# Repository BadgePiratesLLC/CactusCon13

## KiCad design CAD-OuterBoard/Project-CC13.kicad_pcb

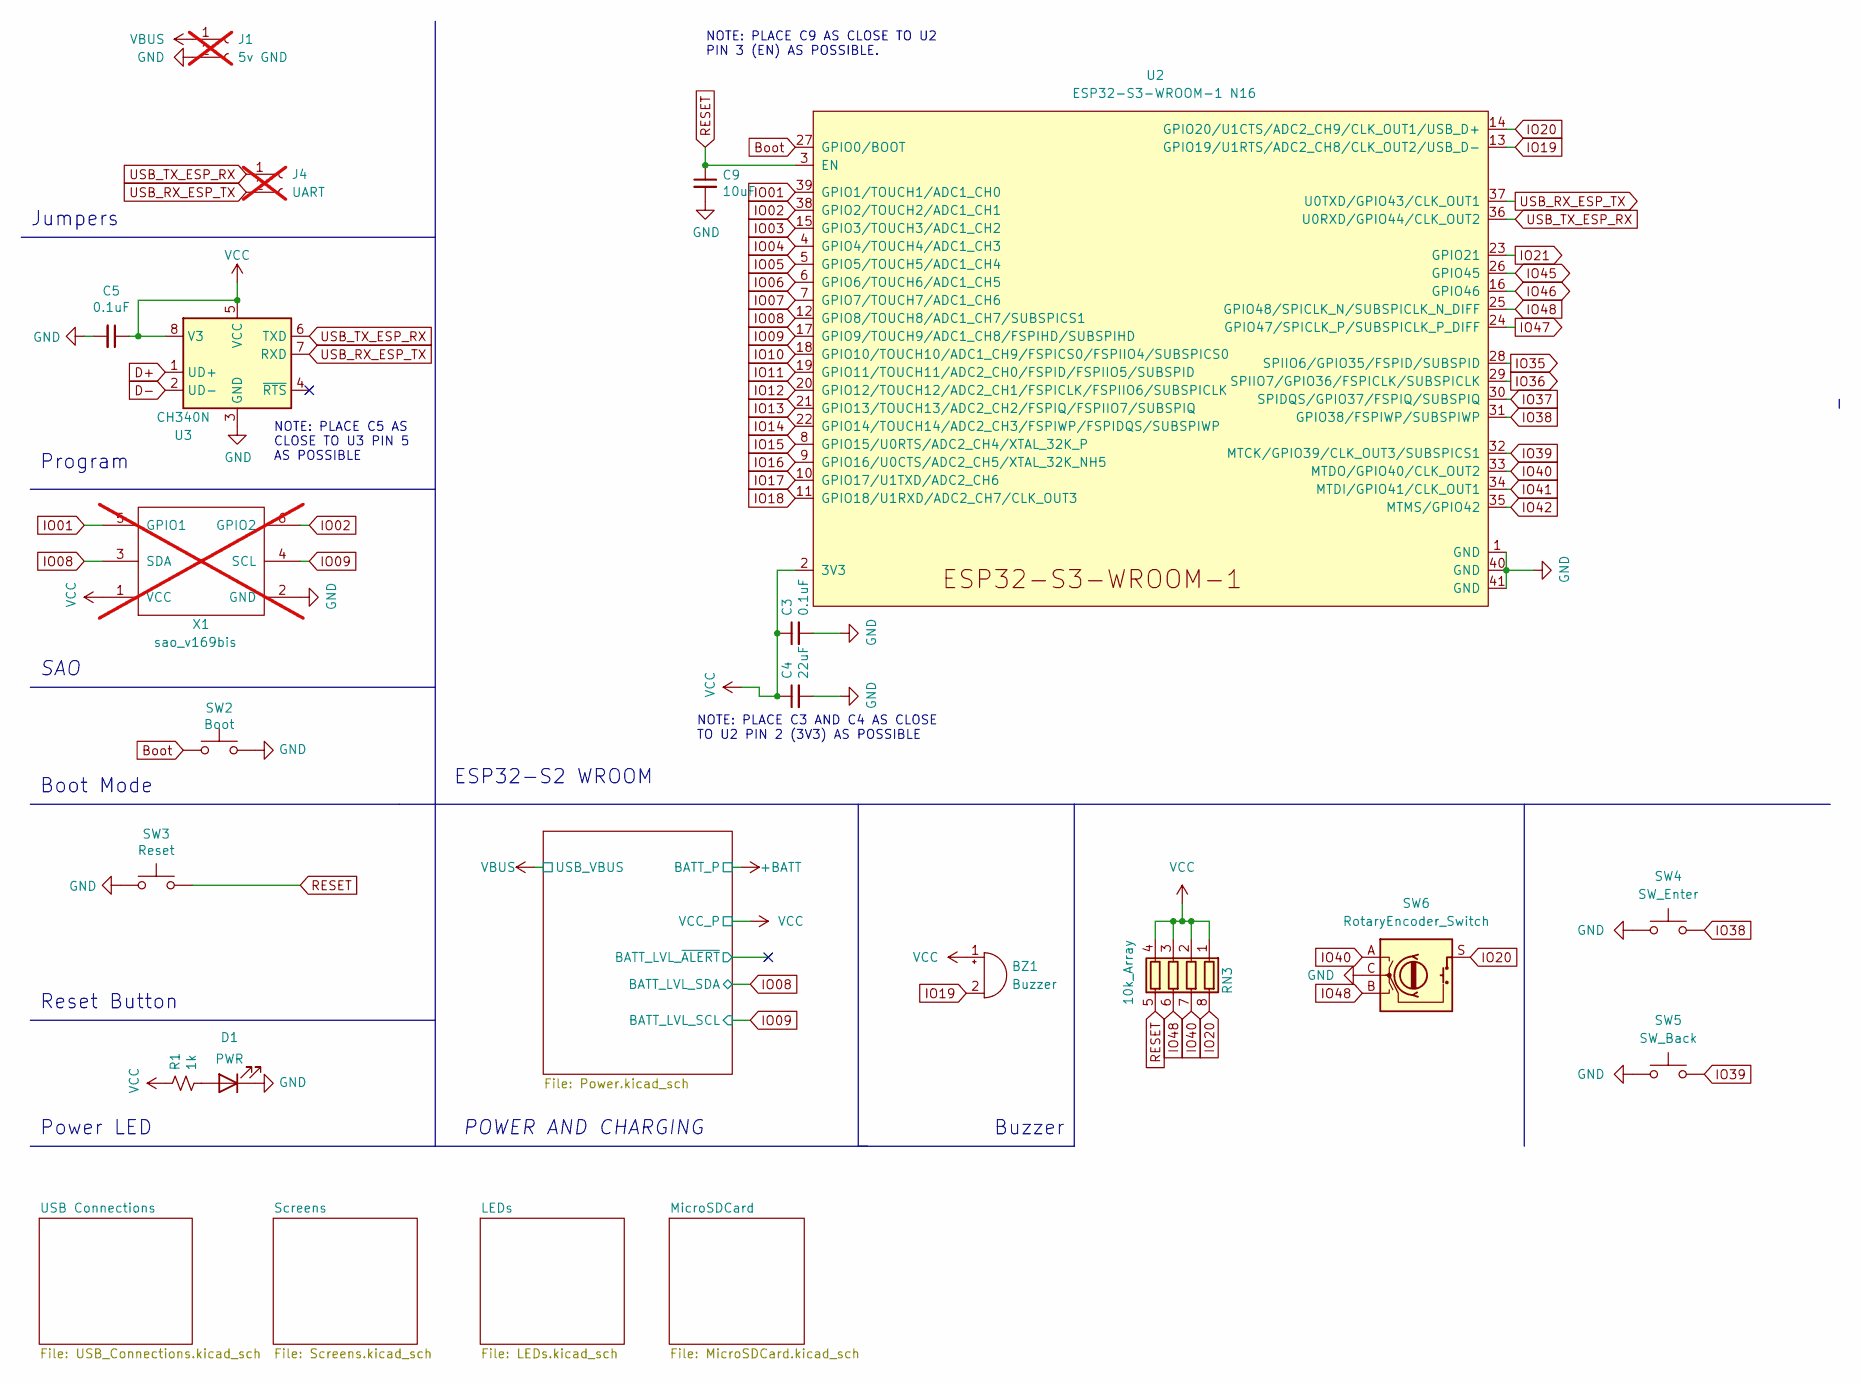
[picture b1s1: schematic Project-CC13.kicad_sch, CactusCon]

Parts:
BZ1: Buzzer; FUET-9032-Buzzer
C3, C5: 0.1uF; C_0805_2012Metric; MFG_PN CT41G-0805-2X1-50V-0.1μF-K(N)
C4: 22uF; C_0805_2012Metric; MFG_PN CL21A226MAYNNNE
C9: 10uF; C_0805_2012Metric; MFG_PN CL21A106KPCLQNC
D1: PWR; LED_1206; MFG_PN NCD1206C1
J1: 5v GND; PinHeader_1x02_P2.54mm_Vertical; not fitted
J4: UART; PinHeader_1x02_P2.54mm_Vertical; not fitted
R1: 1k; R_1206_3216Metric; MFG_PN RC1206FR-071KL
RN3: 10k_Array; R_Array_Convex_4x0603; MFG_PN YC164-RR-0710KL
SW2: Boot; Switch_Tactile_SMD_B3U-1000P-BPVersion; MFG_PN B3U-1000P
SW3: Reset; Switch_Tactile_SMD_B3U-1000P-BPVersion; MFG_PN B3U-1000P
SW4: SW_Enter; SW_SPST_TL3305C(small)
SW5: SW_Back; SW_SPST_TL3305C(small)
SW6: RotaryEncoder_Switch; SIQ-02FVS3_Encoder
U2: ESP32-S3-WROOM-1 N16; ESP32-S3-WROOM-1; MFG_PN ESP32-S3-WROOM-1-N8R8
U3: CH340N; SOIC-8-1EP_W3.9mm; MFG_PN CH340N
X1: sao_v169bis; Badgelife-SAOv169-SAO_Side_B.SLK; not fitted

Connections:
Boot: SW2.1, U2.27 (GPIO0/BOOT)
D+: U3.1 (UD+); also elsewhere on the board
D-: U3.2 (UD-); also elsewhere on the board
GND: C3.2, C4.2, C5.2, C9.2, D1.1 (K), J1.2, SW2.2, SW3.1, SW4.1, SW5.1, SW6.C, U2.1 (GND), U2.40 (GND), U2.41 (GND), U3.3 (GND), X1.2 (GND); also elsewhere on the board
IO01: U2.39 (GPIO1/TOUCH1/ADC1_CH0), X1.5 (GPIO1)
IO02: U2.38 (GPIO2/TOUCH2/ADC1_CH1), X1.6 (GPIO2)
IO03: U2.15 (GPIO3/TOUCH3/ADC1_CH2); also elsewhere on the board
IO04: U2.4 (GPIO4/TOUCH4/ADC1_CH3); also elsewhere on the board
IO05: U2.5 (GPIO5/TOUCH5/ADC1_CH4); also elsewhere on the board
IO06: U2.6 (GPIO6/TOUCH6/ADC1_CH5); also elsewhere on the board
IO07: U2.7 (GPIO7/TOUCH7/ADC1_CH6); also elsewhere on the board
IO08: U2.12 (GPIO8/TOUCH8/ADC1_CH7/SUBSPICS1), X1.3 (SDA); also elsewhere on the board
IO09: U2.17 (GPIO9/TOUCH9/ADC1_CH8/FSPIHD/SUBSPIHD), X1.4 (SCL); also elsewhere on the board
IO10: U2.18 (GPIO10/TOUCH10/ADC1_CH9/FSPICS0/FSPIIO4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); also elsewhere on the board
IO11: U2.19 (GPIO11/TOUCH11/ADC2_CH0/FSPID/FSPIIO5/S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); also elsewhere on the board
IO12: U2.20 (GPIO12/TOUCH12/ADC2_CH1/FSPICLK/FSPIIO6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); also elsewhere on the board
IO13: U2.21 (GPIO13/TOUCH13/ADC2_CH2/FSPIQ/FSPIIO7/S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); also elsewhere on the board
IO14: U2.22 (GPIO14/TOUCH14/ADC2_CH3/FSPIWP/FSPIDQS/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); also elsewhere on the board
IO15: U2.8 (GPIO15/U0RTS/ADC2_CH4/XTAL_32K_P); also elsewhere on the board
IO16: U2.9 (GPIO16/U0CTS/ADC2_CH5/XTAL_32K_NH5); also elsewhere on the board
IO17: U2.10 (GPIO17/U1TXD/ADC2_CH6); also elsewhere on the board
IO18: U2.11 (GPIO18/U1RXD/ADC2_CH7/CLK_OUT3); also elsewhere on the board
IO19: BZ1.2 (+), U2.13 (GPIO19/U1RTS/ADC2_CH8/CLK_OUT2/USB_D-)
IO20: RN3.8 (R1.2), SW6.S, U2.14 (GPIO20/U1CTS/ADC2_CH9/CLK_OUT1/USB_D+); also elsewhere on the board
IO21: U2.23 (GPIO21); also elsewhere on the board
IO35: U2.28 (SPIIO6/GPIO35/FSPID/SUBSPID); also elsewhere on the board
IO36: U2.29 (SPIIO7/GPIO36/FSPICLK/SUBSPICLK); also elsewhere on the board
IO37: U2.30 (SPIDQS/GPIO37/FSPIQ/SUBSPIQ); also elsewhere on the board
IO40: RN3.7 (R2.2), SW6.A, U2.33 (MTDO/GPIO40/CLK_OUT2); also elsewhere on the board
IO41: U2.34 (MTDI/GPIO41/CLK_OUT1)
IO42: U2.35 (MTMS/GPIO42)
IO45: U2.26 (GPIO45)
IO46: U2.16 (GPIO46); also elsewhere on the board
IO47: U2.24 (GPIO47/SPICLK_P/SUBSPICLK_P_DIFF); also elsewhere on the board
IO48: RN3.6 (R3.2), SW6.B, U2.25 (GPIO48/SPICLK_N/SUBSPICLK_N_DIFF); also elsewhere on the board
unnamed: D1.2 (A), R1.2
RESET: C9.1, RN3.5 (R4.2), SW3.2, U2.3 (EN)
USB_RX_ESP_TX: J4.2, U2.37 (U0TXD/GPIO43/CLK_OUT1), U3.7 (RXD)
USB_TX_ESP_RX: J4.1, U2.36 (U0RXD/GPIO44/CLK_OUT2), U3.6 (TXD)
VBUS: J1.1; also elsewhere on the board
VCC: BZ1.1 (-), C3.1, C4.1, C5.1, R1.1, RN3.1 (R1.1), RN3.2 (R2.1), RN3.3 (R3.1), RN3.4 (R4.1), U2.2 (3V3), U3.5 (VCC), U3.8 (V3), X1.1 (VCC); also elsewhere on the board

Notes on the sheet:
Buzzer
POWER AND CHARGING
SAO
Power LED
Jumpers
ESP32-S2 WROOM
NOTE: PLACE C5 AS CLOSE TO U3 PIN 5 AS POSSIBLE
Program
Boot Mode
NOTE: PLACE C3 AND C4 AS CLOSE TO U2 PIN 2 (3V3) AS POSSIBLE
Reset Button
NOTE: PLACE C9 AS CLOSE TO U2 PIN 3 (EN) AS POSSIBLE.

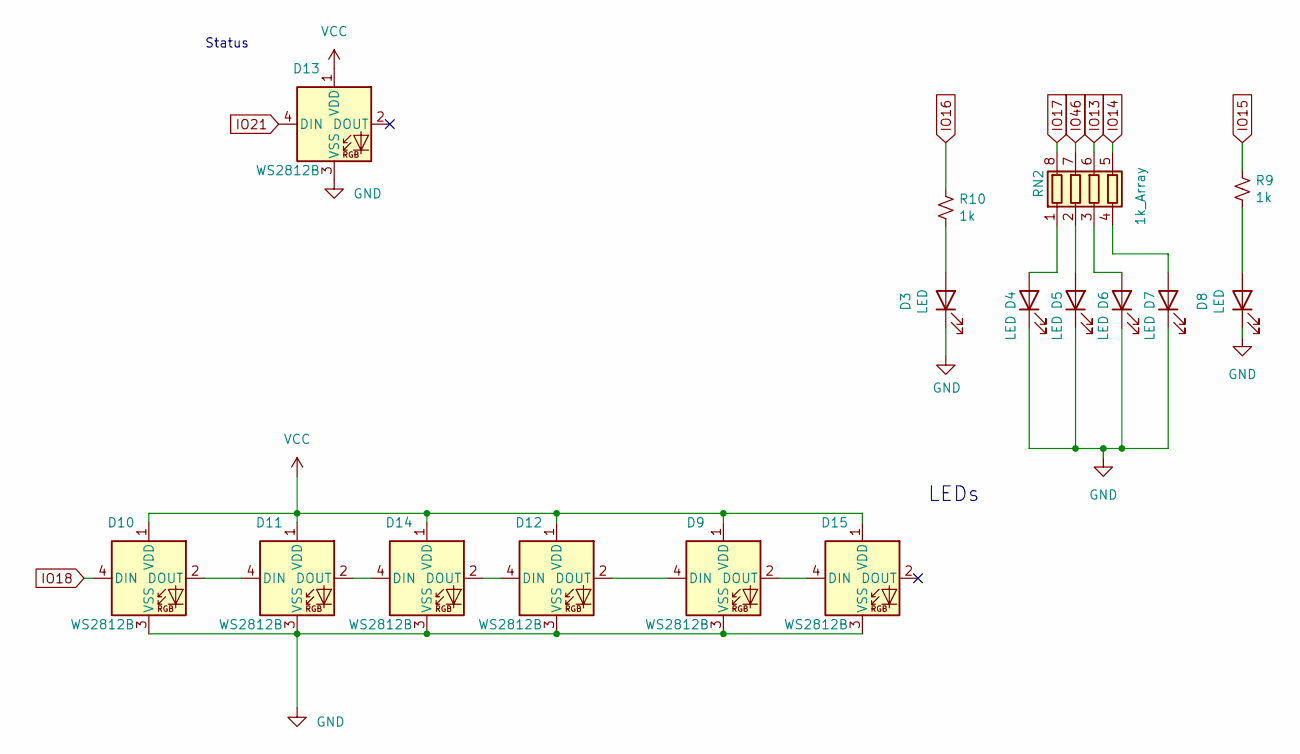
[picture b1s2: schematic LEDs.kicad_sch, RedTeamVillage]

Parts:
D3, D4, D5, D6, D7, D8: LED; LED_Osram_Lx_P47F_D2mm_ReverseMount_Proper_Mask Only; MFG_PN AA3528SYCKT09
D9, D10, D11, D12, D13, D14, D15: WS2812B; LED_WS2812B_PLCC4_5.0x5.0mm_P3.2mm; MFG_PN WS2812B-B/T
R9, R10: 1k; R_1206_3216Metric; MFG_PN RC1206FR-071KL
RN2: 1k_Array; R_Array_Convex_4x0603; MFG_PN YC164-JR-071KL

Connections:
GND: D3.1 (K), D4.1 (K), D5.1 (K), D6.1 (K), D7.1 (K), D8.1 (K), D9.3 (VSS), D10.3 (VSS), D11.3 (VSS), D12.3 (VSS), D13.3 (VSS), D14.3 (VSS), D15.3 (VSS); also elsewhere on the board
IO13: RN2.6 (R3.2); also elsewhere on the board
IO14: RN2.5 (R4.2); also elsewhere on the board
IO15: R9.1; also elsewhere on the board
IO16: R10.1; also elsewhere on the board
IO17: RN2.8 (R1.2); also elsewhere on the board
IO18: D10.4 (DIN); also elsewhere on the board
IO21: D13.4 (DIN); also elsewhere on the board
IO46: RN2.7 (R2.2); also elsewhere on the board
unnamed: D3.2 (A), R10.2
unnamed: D4.2 (A), RN2.1 (R1.1)
unnamed: D5.2 (A), RN2.2 (R2.1)
unnamed: D6.2 (A), RN2.3 (R3.1)
unnamed: D7.2 (A), RN2.4 (R4.1)
unnamed: D8.2 (A), R9.2
unnamed: D10.2 (DOUT), D11.4 (DIN)
unnamed: D11.2 (DOUT), D14.4 (DIN)
unnamed: D12.4 (DIN), D14.2 (DOUT)
unnamed: D9.4 (DIN), D12.2 (DOUT)
unnamed: D9.2 (DOUT), D15.4 (DIN)
VCC: D9.1 (VDD), D10.1 (VDD), D11.1 (VDD), D12.1 (VDD), D13.1 (VDD), D14.1 (VDD), D15.1 (VDD); also elsewhere on the board

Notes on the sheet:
LEDs
Status

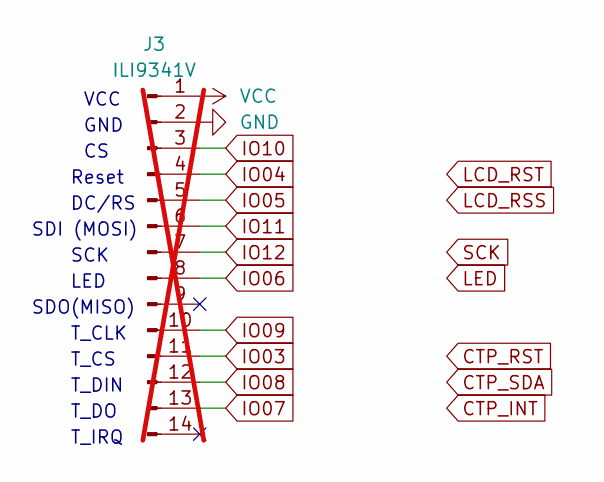
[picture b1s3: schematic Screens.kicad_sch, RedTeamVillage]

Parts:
J3: ILI9341V; PinHeader_1x14_P2.54mm_Vertical; not fitted

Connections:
GND: J3.2; also elsewhere on the board
IO03: J3.11; also elsewhere on the board
IO04: J3.4; also elsewhere on the board
IO05: J3.5; also elsewhere on the board
IO06: J3.8; also elsewhere on the board
IO07: J3.13; also elsewhere on the board
IO08: J3.12; also elsewhere on the board
IO09: J3.10; also elsewhere on the board
IO10: J3.3; also elsewhere on the board
IO11: J3.6; also elsewhere on the board
IO12: J3.7; also elsewhere on the board
VCC: J3.1; also elsewhere on the board

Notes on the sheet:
Reset
SDO(MISO)
SCK
T_CLK
SDI (MOSI)
LED
T_IRQ
T_DO
GND
T_CS
DC/RS
T_DIN
VCC

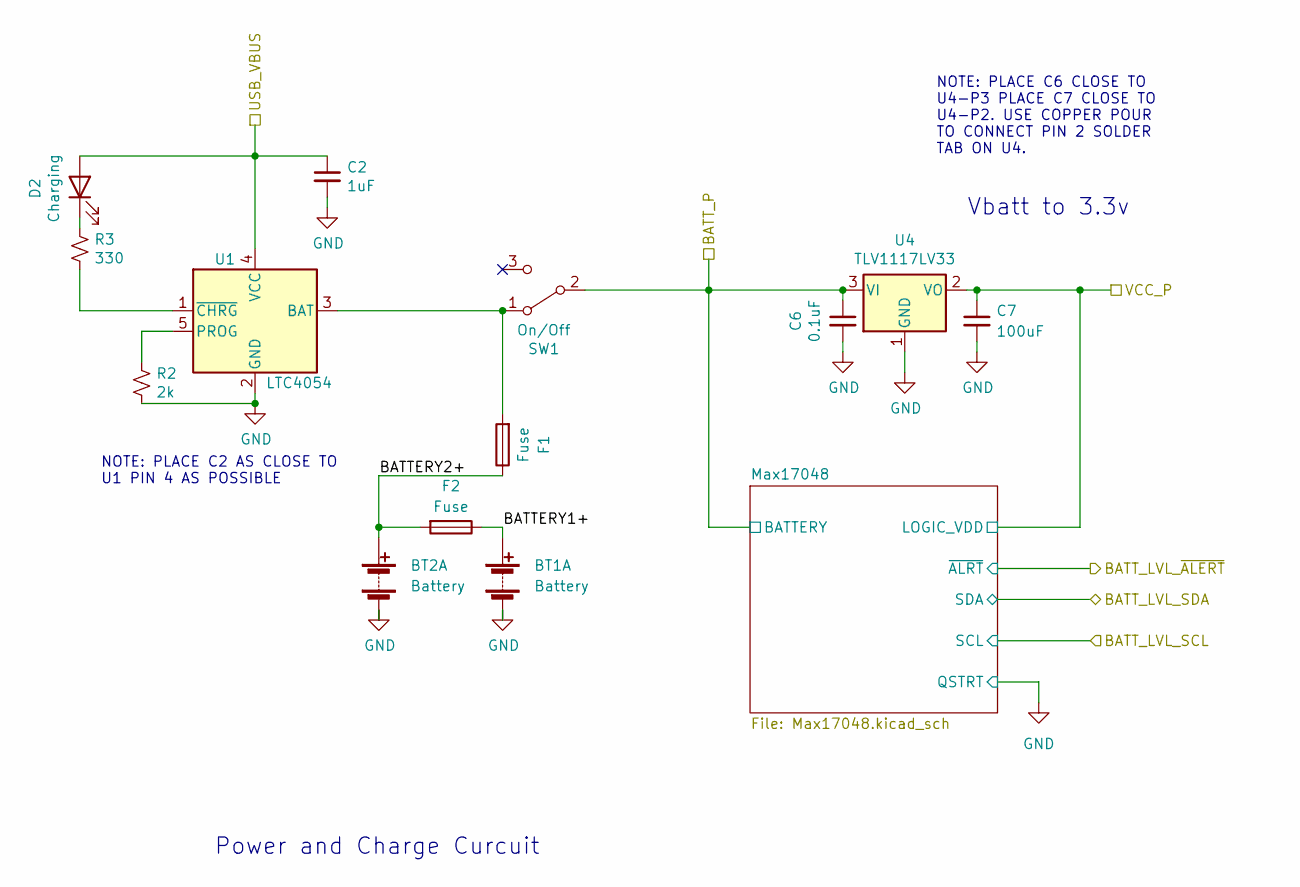
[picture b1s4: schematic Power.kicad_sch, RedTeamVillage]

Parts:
BT1, BT2: Battery; Battery - 14500; MFG_PN 53
C2: 1uF; C_0805_2012Metric; MFG_PN CL21B105KBFNNNE
C6: 0.1uF; C_0805_2012Metric; MFG_PN CT41G-0805-2X1-50V-0.1μF-K(N)
C7: 100uF; 100uf_CP_Pad1.50x2.35mm; MFG_PN TAJB107M006RNJ
D2: Charging; LED_1206; MFG_PN NCD1206B1
F1, F2: Fuse; R_1206_3216Metric; MFG_PN TLC-NSMD200
R2: 2k; R_1206_3216Metric; MFG_PN RC1206FR-072KL
R3: 330; R_1206_3216Metric; MFG_PN AC1206JR-07330KL
SW1: On/Off; SW_SPDT_PCM12; MFG_PN SSSS811101
U1: LTC4054; MFG_PN TP4054ST25K
U4: TLV1117LV33; SOT-223; MFG_PN TLV1117LV33DCYR

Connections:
+BATT: C6.1, SW1.2 (B), U4.3 (VI); also elsewhere on the board
/Power and Charge Curcuit/BATTERY1+: BT1.1 (+), F2.1
/Power and Charge Curcuit/BATTERY2+: BT2.1 (+), F1.1, F2.2
GND: BT1.2 (-), BT2.2 (-), C2.2, C6.2, C7.2, R2.2, U1.2 (GND), U4.1 (GND); also elsewhere on the board
unnamed: D2.1 (K), R3.1
unnamed: F1.2, SW1.1 (A), U1.3 (BAT)
unnamed: R2.1, U1.5 (PROG)
unnamed: R3.2, U1.1 (~CHRG)
VBUS: C2.1, D2.2 (A), U1.4 (VCC); also elsewhere on the board
VCC: C7.1, U4.2 (VO), U4.4 (VO); also elsewhere on the board

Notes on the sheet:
Power and Charge Curcuit
NOTE: PLACE C2 AS CLOSE TO U1 PIN 4 AS POSSIBLE
NOTE: PLACE C6 CLOSE TO U4-P3 PLACE C7 CLOSE TO U4-P2. USE COPPER POUR TO CONNECT PIN 2 SOLDER TAB ON U4.
Vbatt to 3.3v

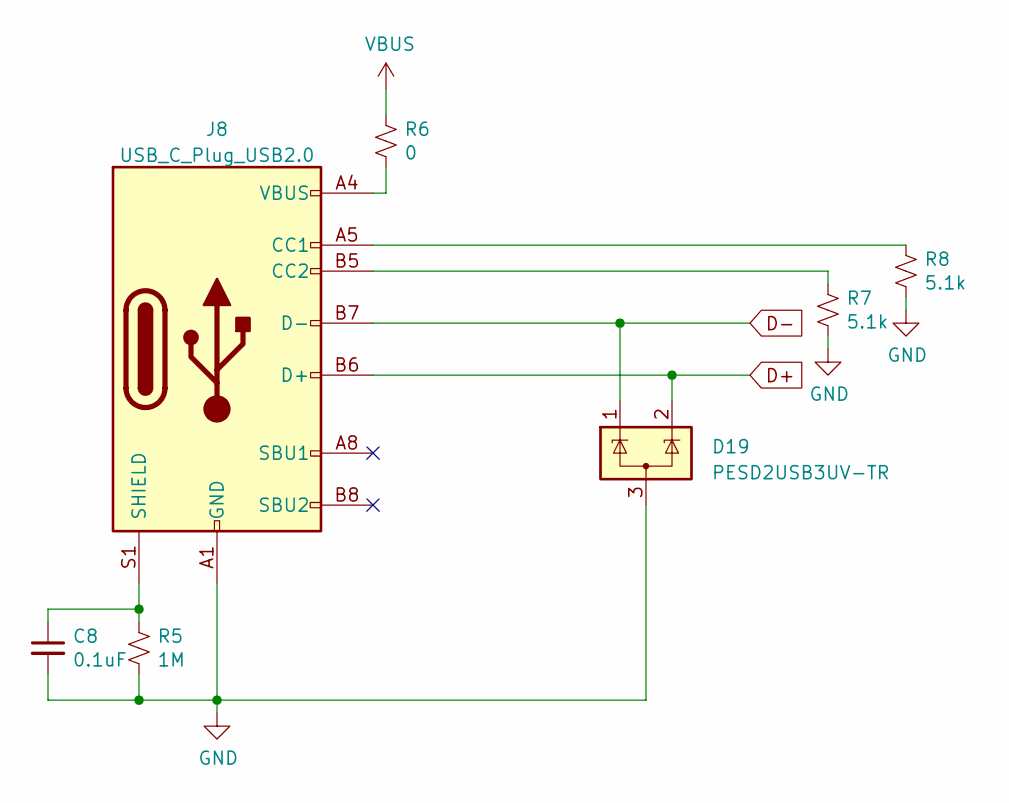
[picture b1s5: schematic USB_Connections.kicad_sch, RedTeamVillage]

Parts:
C8: 0.1uF; C_0805_2012Metric; MFG_PN CT41G-0805-2X1-50V-0.1μF-K(N)
D19: PESD2USB3UV-TR; SOT-23; MFG_PN PESD2USB3UV-TR
J8: USB_C_Plug_USB2.0; USB_C_Receptical-Jing; MFG_PN 918-418K2023S40019
R5: 1M; R_1206_3216Metric; MFG_PN RC1206FR-071ML
R6: 0; R_1206_3216Metric; MFG_PN 1206W4F0000T5E
R7, R8: 5.1k; R_1206_3216Metric; MFG_PN RC1206FR-075K1L

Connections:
D+: D19.2 (K), J8.A6 (D+), J8.B6 (D+); also elsewhere on the board
D-: D19.1 (K), J8.A7 (D-), J8.B7 (D-); also elsewhere on the board
GND: C8.2, D19.3 (A), J8.A1 (GND), J8.A12 (GND), J8.B1 (GND), J8.B12 (GND), R5.2, R7.2, R8.2; also elsewhere on the board
unnamed: J8.A5 (CC1), R8.1
unnamed: J8.B5 (CC2), R7.1
unnamed: C8.1, J8.S1 (SHIELD), R5.1
unnamed: J8.A4 (VBUS), J8.A9 (VBUS), J8.B4 (VBUS), J8.B9 (VBUS), R6.2
VBUS: R6.1; also elsewhere on the board

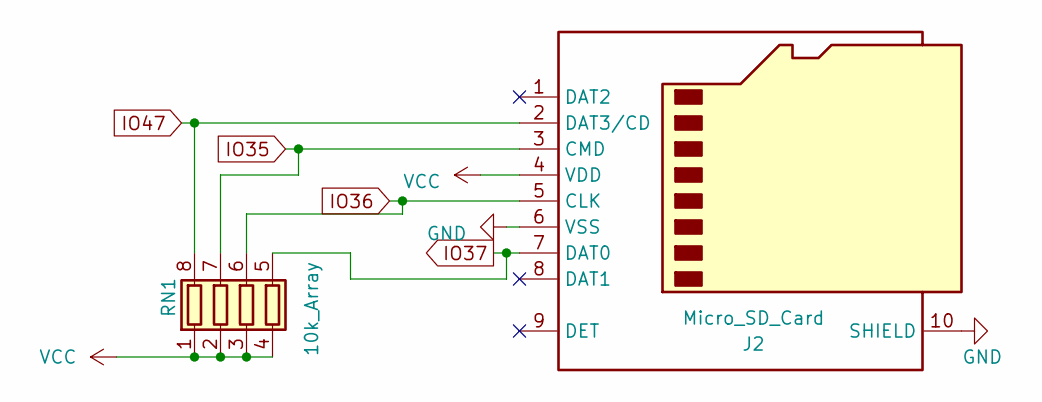
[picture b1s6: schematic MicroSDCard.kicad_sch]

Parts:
J2: Micro_SD_Card; TF_PUSH; MFG_PN TF PUSH
RN1: 10k_Array; R_Array_Convex_4x0603; MFG_PN YC164-RR-0710KL

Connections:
GND: J2.6 (VSS), J2.10 (SHIELD); also elsewhere on the board
IO35: J2.3 (CMD), RN1.7 (R2.2); also elsewhere on the board
IO36: J2.5 (CLK), RN1.6 (R3.2); also elsewhere on the board
IO37: J2.7 (DAT0), RN1.5 (R4.2); also elsewhere on the board
IO47: J2.2 (DAT3/CD), RN1.8 (R1.2); also elsewhere on the board
VCC: J2.4 (VDD), RN1.1 (R1.1), RN1.2 (R2.1), RN1.3 (R3.1), RN1.4 (R4.1); also elsewhere on the board

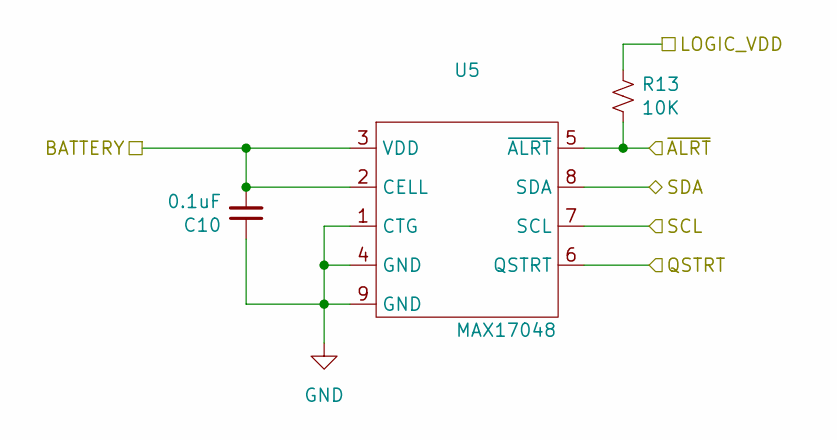
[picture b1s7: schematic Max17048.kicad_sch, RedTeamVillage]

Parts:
C10: 0.1uF; C_0805_2012Metric; MFG_PN CT41G-0805-2X1-50V-0.1μF-K(N)
R13: 10K; R_1206_3216Metric; MFG_PN RC1206FR-0710KL
U5: MAX17048; MAX17048_TDFN; MFG_PN MAX17048G+

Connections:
+BATT: C10.2, U5.2 (CELL), U5.3 (VDD); also elsewhere on the board
/Power and Charge Curcuit/BATT_LVL_~ALERT: R13.2, U5.5 (~ALRT)
GND: C10.1, U5.1 (CTG), U5.4 (GND), U5.6 (QSTRT), U5.9 (GND); also elsewhere on the board
IO08: U5.8 (SDA); also elsewhere on the board
IO09: U5.7 (SCL); also elsewhere on the board
VCC: R13.1; also elsewhere on the board

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
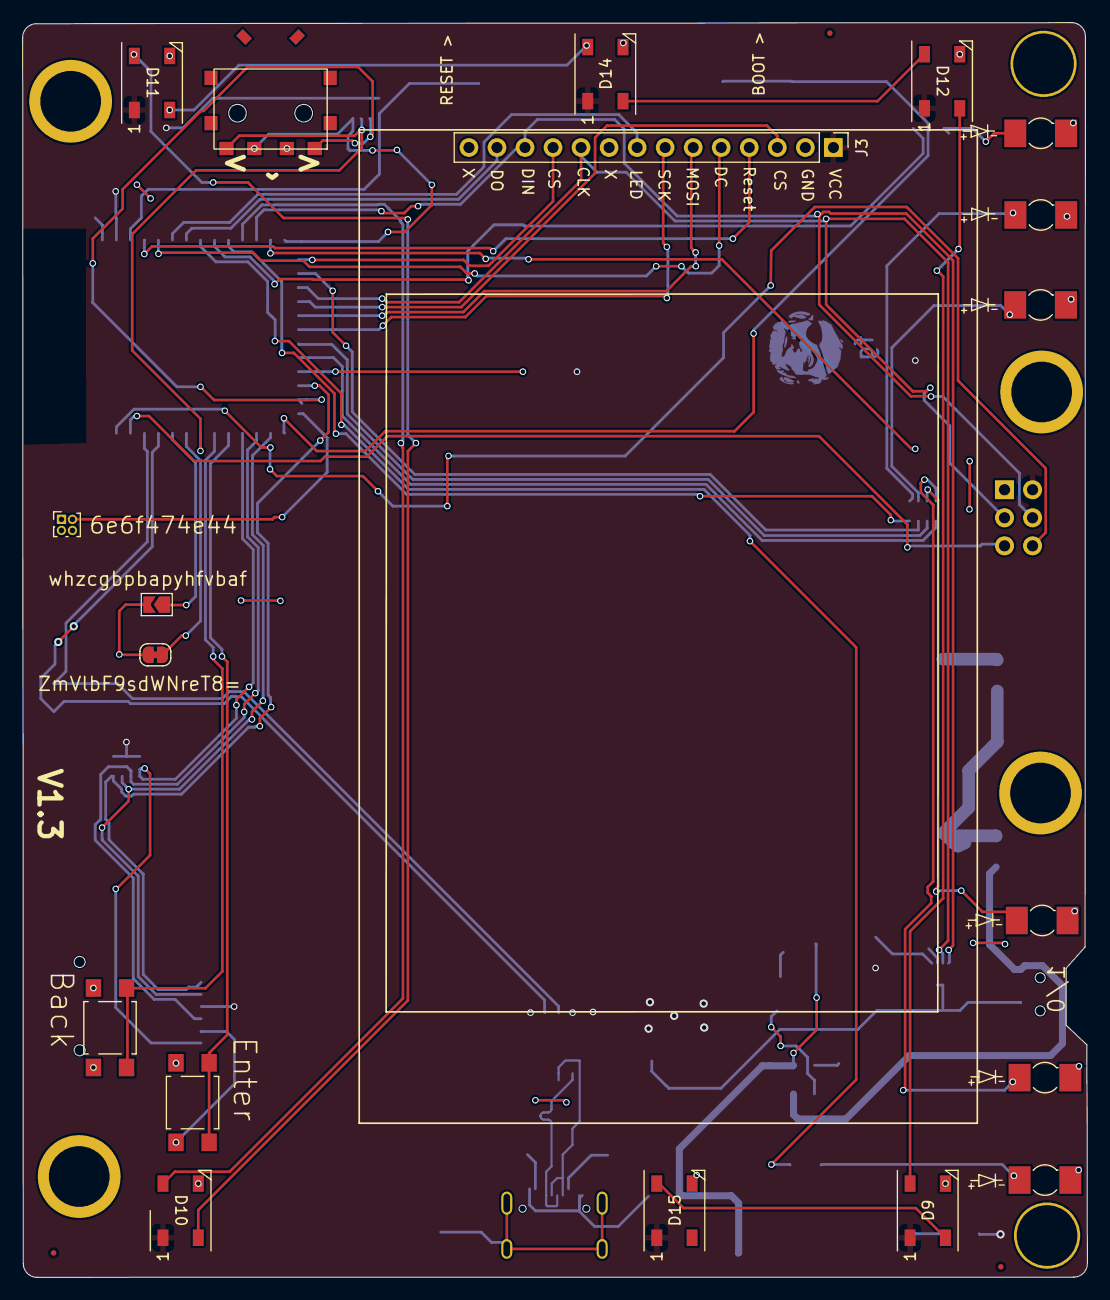
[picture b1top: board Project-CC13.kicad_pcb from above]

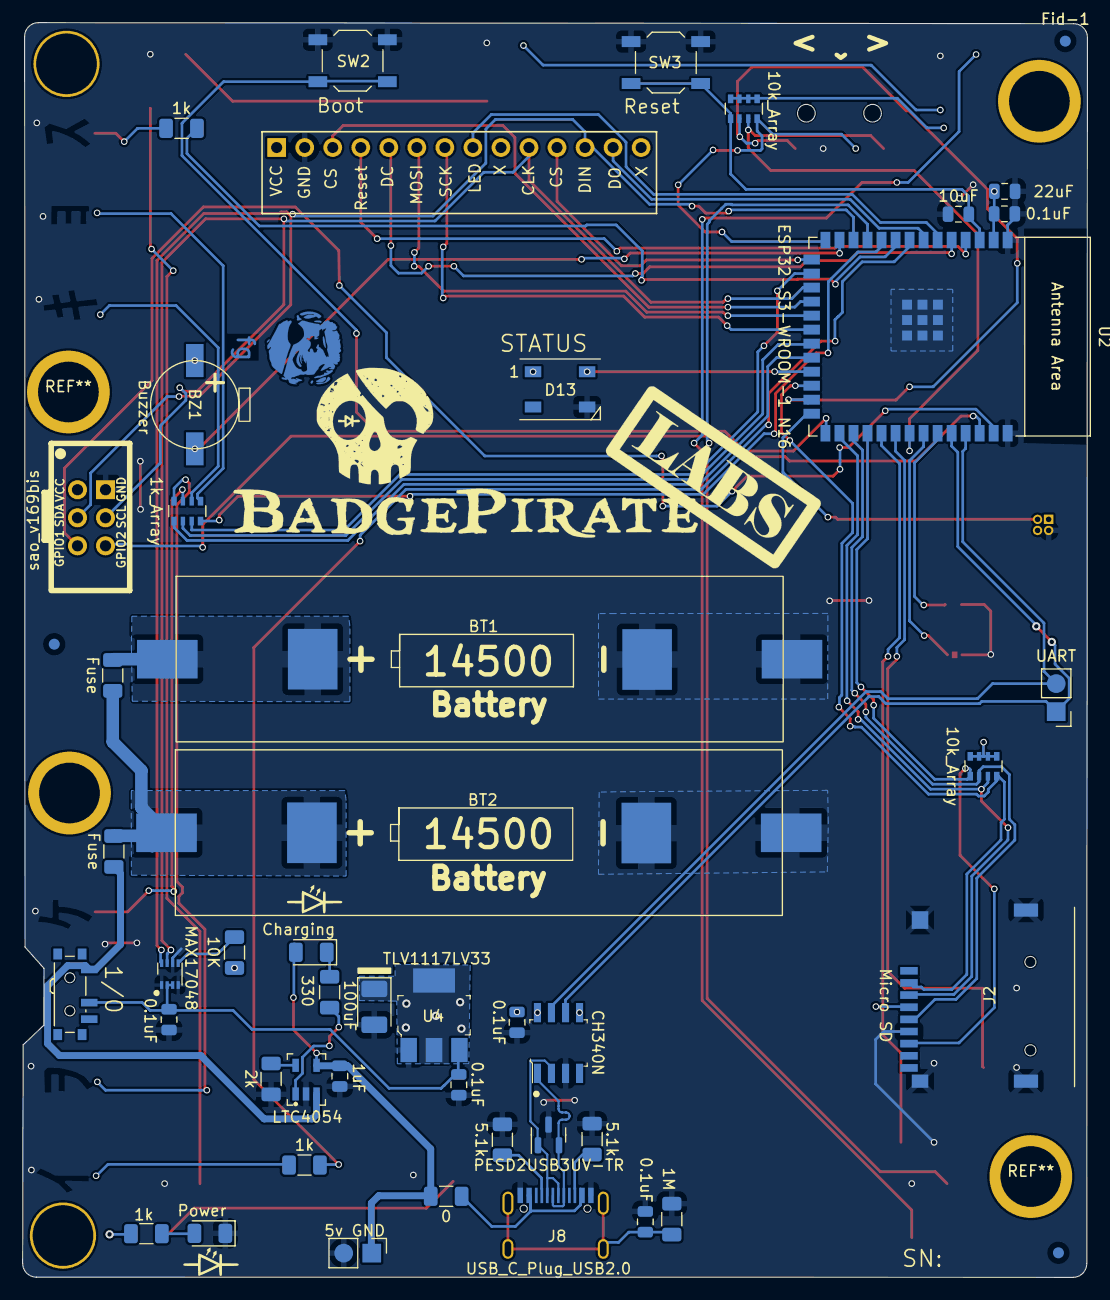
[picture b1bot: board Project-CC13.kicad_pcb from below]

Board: 2 copper layers, 96.5 x 113.7 mm, 67 parts (47 on the bottom side), 63 nets.

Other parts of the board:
Fid-1, Fid-2, Fid-3: Fiducial_1mm_Mask2mm
Fid-4, Fid-5, Fid-6: Fiducial_0.5mm_Mask1mm
Ref**: Val**; BadgePiratesLabs
SW8: SW_Center; SW_SPST_TL3305C(small)
SW10: RotaryEncoder_Switch; SIQ-02FVS3_Encoder

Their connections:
GND: SW8.1, SW10.C; also elsewhere on the board
IO20: SW10.S; also elsewhere on the board
IO40: SW10.A; also elsewhere on the board
IO48: SW10.B; also elsewhere on the board

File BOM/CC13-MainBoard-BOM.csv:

Reference,Qty,Value,Footprint,MPN,LCSC#,Manufacturer,DNP
"BT1,BT2",2,Battery,BadgePirates:Battery - 14500,53,,Keystone Electronics,
BZ1,1,Buzzer,BadgePirates:FUET-9032-Buzzer,FUET-9032,,Fuet Electronics,
C2,1,1uF,BadgePirates:C_0805_2012Metric,CL21B105KBFNNNE,C28323,Samsung Electro-Mechanics,
"C3,C5,C6,C8,C10",5,0.1uF,BadgePirates:C_0805_2012Metric,CT41G-0805-2X1-50V-0.1μF-K(N),C126469,TORCH ,
C4,1,22uF,BadgePirates:C_0805_2012Metric,CL21A226MAYNNNE,C602037,Samsung Electro-Mechanics,
C7,1,100uF,BadgePirates:100uf_CP_Pad1.50x2.35mm,TAJB107M006RNJ,C7195,KYOCERA AVX,
C9,1,10uF,BadgePirates:C_0805_2012Metric,CL21A106KPCLQNC,C962097,Samsung Electro-Mechanics,
D1,1,PWR,BadgePirates:LED_1206,NCD1206C1,C84273,Foshan NationStar Optoelectronics,
D2,1,Charging,BadgePirates:LED_1206,NCD1206B1,C130717,Foshan NationStar Optoelectronics,
D3-D8,6,LED,BadgePirates:LED_Osram_Lx_P47F_D2mm_ReverseMount_Proper_Mask Only,AA3528SYCKT09,,KingBright,
"D9,D14,D15",3,WS2812B,BadgePiratesFootprints:LED_WS2812B_PLCC4_5.0x5.0mm_P3.2mm,WS2812B-B/T,C2761795,Worldsemi,
D10-D13,4,WS2812B,BadgePirates:LED_WS2812B_PLCC4_5.0x5.0mm_P3.2mm,WS2812B-B/T,C2761795,Worldsemi,
D19,1,PESD2USB3UV-TR,BadgePirates:SOT-23,PESD2USB3UV-TR,C7202955,TECH PUBLIC,
"F1,F2",2,Fuse,BadgePirates:R_1206_3216Metric,TLC-NSMD200,C261957,TLC Electronic,
J2,1,Micro_SD_Card,BadgePirates:TF_PUSH,TF PUSH,C393941,SHOU HAN,
J3,1, ILI9341V,Connector_PinHeader_2.54mm:PinHeader_1x14_P2.54mm_Vertical,,,,DNP
J8,1,USB_C_Plug_USB2.0,BadgePirates:USB_C_Receptical-Jing,918-418K2023S40019,C709035,Jing Extension of the Electronic Co.,
"R1,R9,R10",3,1k,BadgePirates:R_1206_3216Metric,RC1206FR-071KL,C131398,YAGEO,
R2,1,2k,BadgePirates:R_1206_3216Metric,RC1206FR-072KL,C133543,YAGEO,
R3,1,330,BadgePirates:R_1206_3216Metric,AC1206JR-07330KL,C229929,YAGEO,
R5,1,1M,BadgePirates:R_1206_3216Metric,RC1206FR-071ML,C108083,YAGEO,
R6,1,0,BadgePirates:R_1206_3216Metric,1206W4F0000T5E,C17888,UNI-ROYAL(Uniroyal Elec) ,
"R7,R8",2,5.1k,BadgePirates:R_1206_3216Metric,RC1206FR-075K1L,C163372,YEGEO,
R13,1,10K,BadgePirates:R_1206_3216Metric,RC1206FR-0710KL,C132649,YAGEO,
"RN1,RN3",2,10k_Array,BadgePirates:R_Array_Convex_4x0603,YC164-RR-0710KL,C110924,YAGEO,
RN2,1,1k_Array,BadgePirates:R_Array_Convex_4x0603,YC164-JR-071KL,C93675,YAGEO,
SW1,1,On/Off,BadgePirates:SW_SPDT_PCM12,SSSS811101,C109335,ALPSALPINE,
SW2,1,Boot,BadgePirates:Switch_Tactile_SMD_B3U-1000P-BPVersion,B3U-1000P,C231329,Omron Electronics,
SW3,1,Reset,BadgePirates:Switch_Tactile_SMD_B3U-1000P-BPVersion,B3U-1000P,C231329,Omron Electronics,
SW4,1,SW_Enter,BadgePirates:SW_SPST_TL3305C(small),,,,
SW5,1,SW_Back,BadgePirates:SW_SPST_TL3305C(small),,,,
SW6,1,RotaryEncoder_Switch,BadgePirates:SIQ-02FVS3_Encoder,,,,
U1,1,LTC4054,BadgePirates:LTC4054,TP4054ST25K,TP4054ST25K,TPOWER,
U2,1,ESP32-S3-WROOM-1 N16,BadgePirates:ESP32-S3-WROOM-1,ESP32-S3-WROOM-1-N8R8,C2913200,ESPRESSIF,
U3,1,CH340N,BadgePirates:SOIC-8-1EP_W3.9mm,CH340N,C2977777,WCH(Jiangsu Qin Heng),
U4,1,TLV1117LV33,BadgePirates:SOT-223,TLV1117LV33DCYR,C15578,Texas Instruments,
U5,1,MAX17048,BadgePirates:MAX17048_TDFN,MAX17048G+,C2682616,Analog Devices Inc,

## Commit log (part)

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2025-03-16 Upload
